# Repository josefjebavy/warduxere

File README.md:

Warduxere
===========================================
Wireless Arduino with low power consumption

Warduxere (old name was Warduino) was awarded the prize in a magazine for the design of electronic journals [PE-AR](http://www.aradio.cz/). 
### About ###
This project is open-source alternative for other proprietary platform.

It is base on Arduino - CPU AVR ATmega328.
This device is designed for wireless comunication and long run on battery.

### Using 
directories contain
- arduino - example program for arduino - wiring language
- pcb - scheme in Kicad and pcb

## Scheme

## 3D view of device
First model from year 2014.

warduxere DPS v2

[warduxere documentation](https://blog.josefjebavy.cz/warduxere)

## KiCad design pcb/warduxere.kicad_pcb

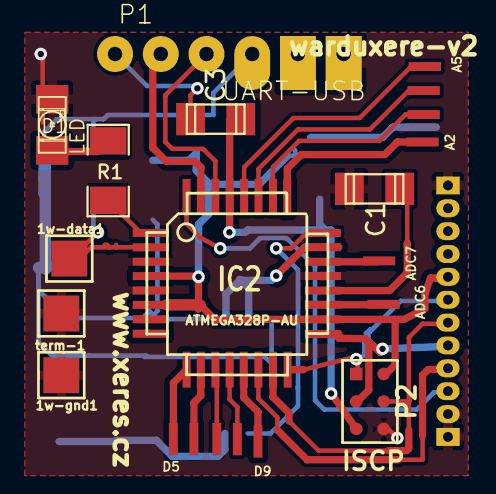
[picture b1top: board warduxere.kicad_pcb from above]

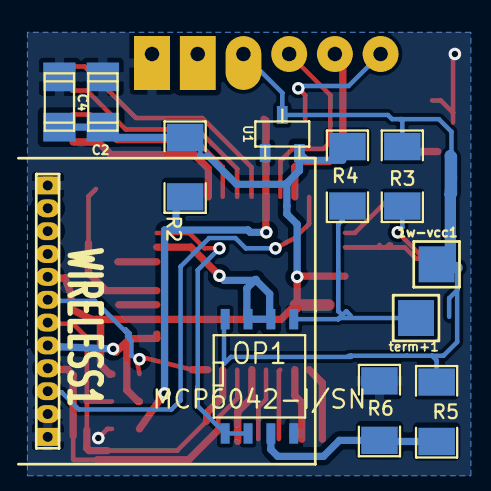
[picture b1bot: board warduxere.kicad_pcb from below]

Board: 2 copper layers, 33 parts (12 on the bottom side), 31 nets.

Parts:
1w-data1, 1w-gnd1, 1w-vcc1: CONN_1; 1PIN_SMDx
A2, A3, A4, A5: CONN_1; 1PIN_SMDxx
ADC6, ADC7: CONN_1; 1PIN_SMDxx
C1, C2, C3: 100n; c_1206
C4: 10u; c_1206
D1: LED; LED-1206
D5, D6, D7, D8, D9: CONN_1; 1PIN_SMDxx
IC2: ATMEGA328P-AU; TQFP32
OP1: MCP6042-I/SN; SO8N
P1: UART-USB; PINHEAD1-6x+
P2: ISCP; pin_array_3x2X-ISCP
R1: 330R; SM1206
R2, R4: 10K; SM1206
R3: 4K7; SM1206
R5, R6: 1M; SM1206
U1: MCP1700T-3302E/TT; sot23
WIRELESS1: SI4432; si4432
term+1: CONN_1; 1PIN_SMDx
term-1: CONN_1; 1PIN_SMDx

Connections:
+3.3V: C2.1, C4.1, IC2.4, IC2.6, IC2.18, P2.2, R2.1, R4.1, U1.3, WIRELESS1.5
+5V: 1w-vcc1.1, OP1.8, P1.4, R3.1, R5.1, U1.2
GND: 1w-gnd1.1, C1.2, C2.2, C4.2, D1.2, IC2.3, IC2.5, IC2.21, OP1.4, P1.6, P2.6, R6.2, U1.1, WIRELESS1.1, WIRELESS1.11, WIRELESS1.12, term-1.1
unnamed: IC2.24, OP1.1, OP1.2
unnamed: IC2.32, WIRELESS1.10
unnamed: IC2.23, OP1.6, OP1.7
unnamed: OP1.5, R4.2, term+1.1
unnamed: OP1.3, R5.2, R6.1
unnamed: IC2.17, P2.3, WIRELESS1.8
unnamed: C3.2, IC2.29, P2.5, R2.2
unnamed: IC2.14, WIRELESS1.9
unnamed: IC2.15, P2.4, WIRELESS1.7
unnamed: D1.1, R1.1
unnamed: IC2.16, P2.1, WIRELESS1.6
unnamed: C1.1, IC2.20
unnamed: 1w-data1.1, IC2.2, R3.2
unnamed: IC2.31, P1.2
unnamed: ADC6.1, IC2.19
unnamed: A5.1, IC2.28
unnamed: A4.1, IC2.27
unnamed: C3.1, P1.1
unnamed: IC2.1, R1.2
unnamed: D8.1, IC2.12
unnamed: A3.1, IC2.26
unnamed: A2.1, IC2.25
unnamed: D9.1, IC2.13
unnamed: ADC7.1, IC2.22
unnamed: D7.1, IC2.11
unnamed: IC2.30, P1.3
unnamed: D6.1, IC2.10
unnamed: D5.1, IC2.9

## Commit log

2015-11-12 add example programs
2015-11-19 text correction
2016-01-09 readme - add scheme
2016-01-09 add Kicad project: scheme,PCB,...
2016-01-09 add bootloader
2016-01-10 add 3d view
2016-01-10 edit image
2016-01-11 edited text
2016-01-11 edit formating of text
2016-02-03 change string Warduino to Warduxere
2016-02-03 bootloader file rename
2016-02-07 rename pcb files
2018-07-19 update name and URL
2018-08-02 DPS version2
2018-08-02 warduxere DPS v2
